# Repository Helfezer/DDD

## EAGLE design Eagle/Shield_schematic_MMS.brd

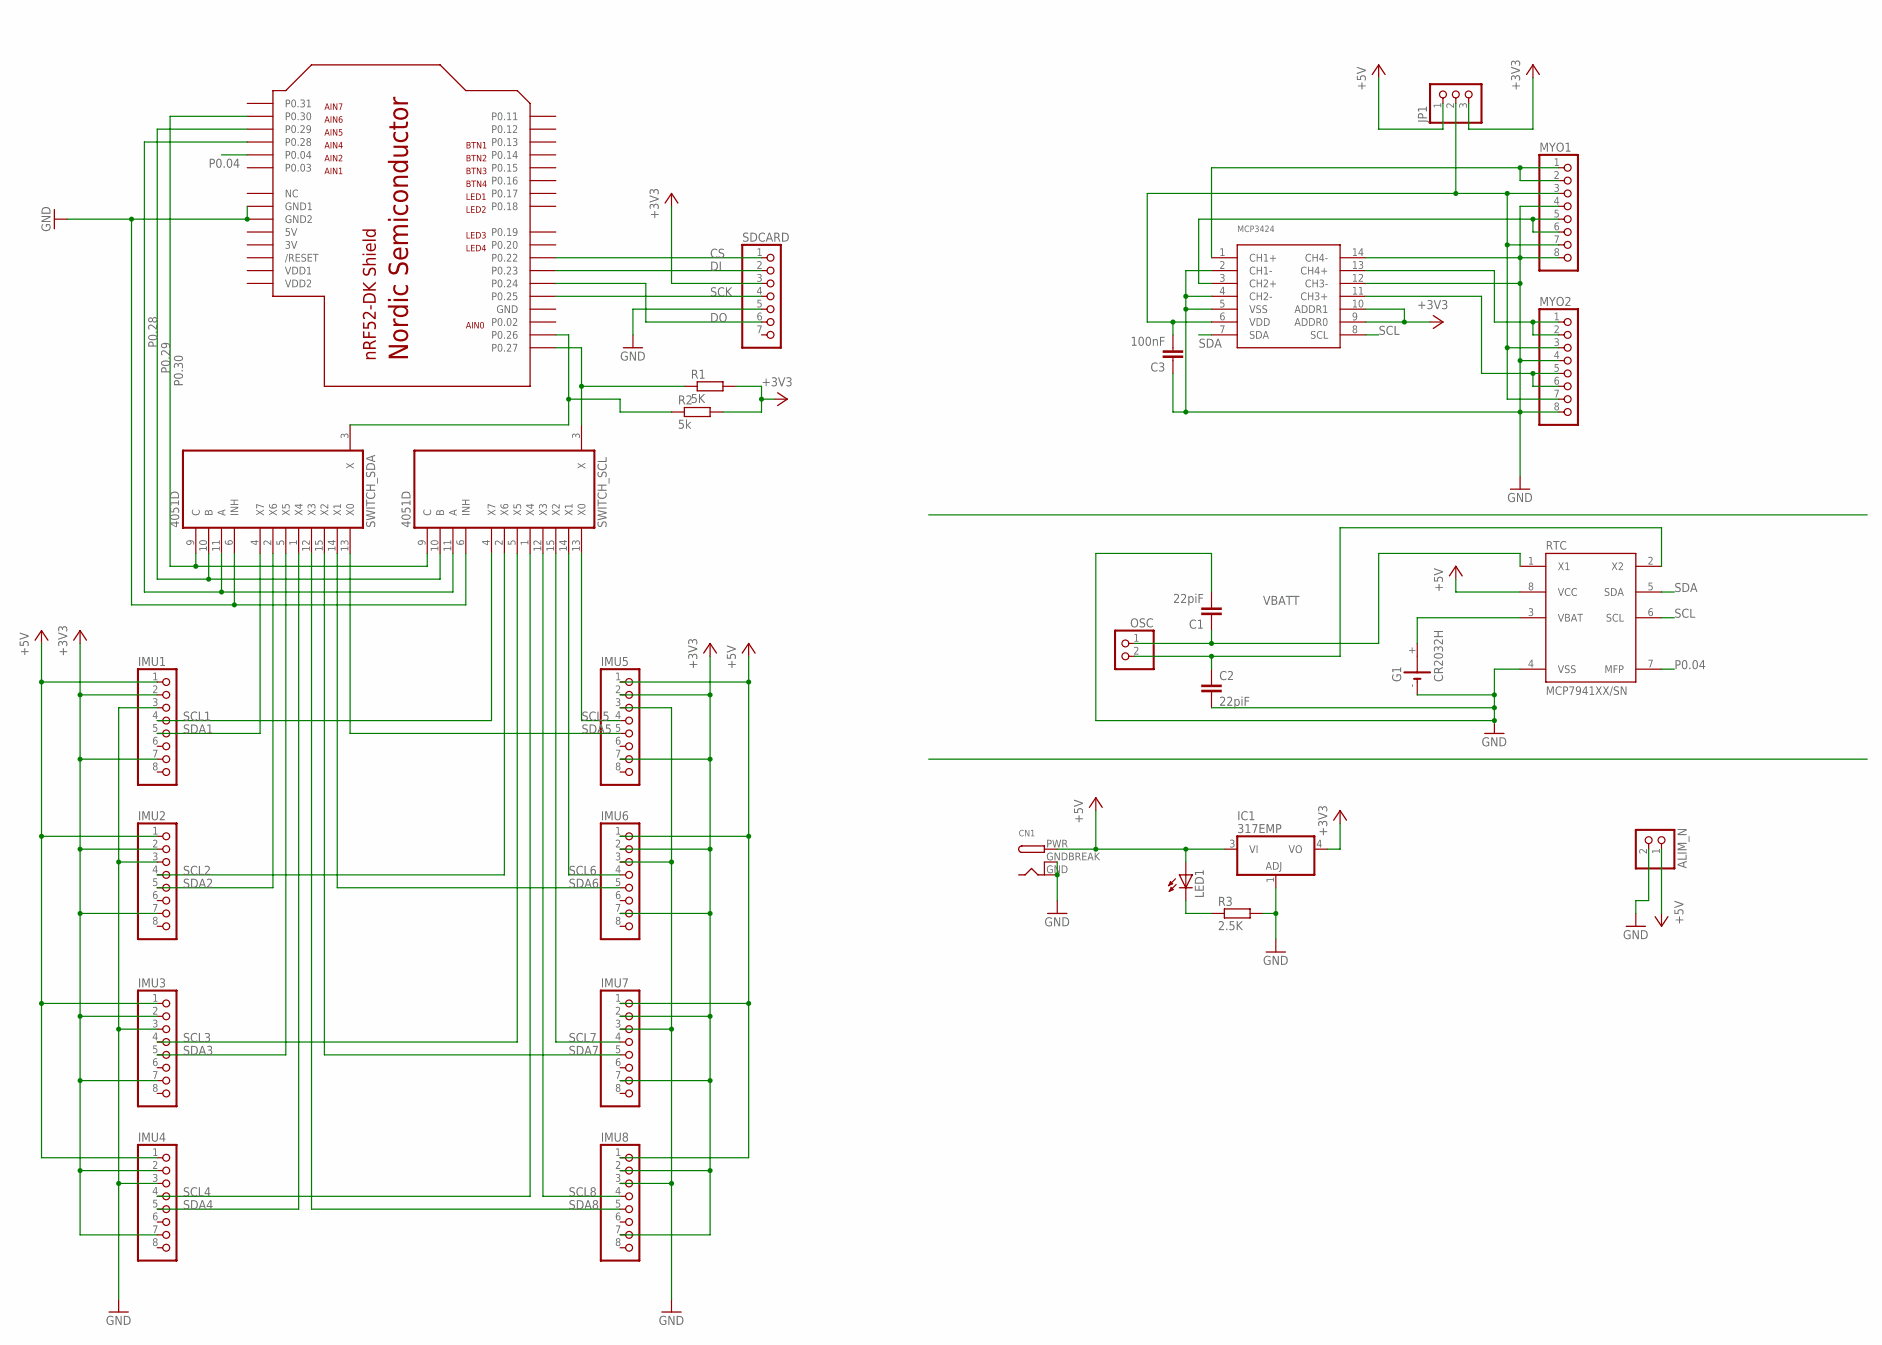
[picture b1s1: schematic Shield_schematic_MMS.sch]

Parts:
ALIM_N: PINHD-1X2; 1X02
C1, C2: 22piF; C2.5-2
C3: 100nF; C2.5-2
CN1: DCBARRELPTH; DCJACK_2MM_PTH
G1: CR2032H
IC1: 317EMP; SOT223
IMU1, IMU2, IMU3, IMU4, IMU5, IMU6, IMU7, IMU8: PINHD-1X8; 1X08
JP1: PINHD-1X3; 1X03
LED1: LEDCHIPLED_1206; CHIPLED_1206
MYO1, MYO2: PINHD-1X8; 1X08
OSC: PINHD-1X2; 1X02
R1: 5K; M1206
R2: 5k; M1206
R3: 2.5K; M1206
RTC: MCP7941XX/SN; SO8
SDCARD: PINHD-1X7; 1X07
SWITCH_SCL: 4051D; SO16
SWITCH_SDA: 4051D; SO16
U$2: NRF52-SHIELD-NOTEXT; NRF52-SHIELD
U$3: MCP3424; SO14

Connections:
3V: U$2.3V
5V: U$2.5V
+3V3: IC1.4 (VO), IMU1.2, IMU1.7, IMU2.2, IMU2.7, IMU3.2, IMU3.7, IMU4.2, IMU4.7, IMU5.2, IMU5.7, IMU6.2, IMU6.7, IMU7.2, IMU7.7, IMU8.2, IMU8.7, JP1.3, R1.2, R2.2, SDCARD.3, U$3.9 (ADDR0), U$3.10 (ADDR1)
+5V: ALIM_N.1, CN1.PWR, IC1.3 (VI), IMU1.1, IMU2.1, IMU3.1, IMU4.1, IMU5.1, IMU6.1, IMU7.1, IMU8.1, JP1.1, LED1.A, RTC.8 (VCC)
CH1: MYO1.1, MYO1.2, U$3.1 (CH1+)
CH2: MYO1.5, MYO1.6, U$3.3 (CH2+)
CH3: MYO2.5, MYO2.6, U$3.11 (CH3+)
CH4: MYO2.1, MYO2.2, U$3.13 (CH4+)
CS: SDCARD.1, U$2.P22 (P0.22)
DI: SDCARD.2, U$2.P23 (P0.23)
DO: SDCARD.6, U$2.P24 (P0.24)
GND: ALIM_N.2, C1.2, C2.2, C3.1, CN1.GND, CN1.GNDBREAK, G1.-, IC1.1 (ADJ), IMU1.3, IMU2.3, IMU3.3, IMU4.3, IMU5.3, IMU6.3, IMU7.3, IMU8.3, MYO1.4, MYO1.8, MYO2.4, MYO2.8, R3.2, RTC.4 (VSS), SDCARD.5, SWITCH_SCL.6 (INH), SWITCH_SCL.8 (GND), SWITCH_SDA.6 (INH), SWITCH_SDA.8 (GND), U$2.GND, U$2.GND1, U$2.GND2, U$3.2 (CH1-), U$3.4 (CH2-), U$3.5 (VSS), U$3.12 (CH3-), U$3.14 (CH4-)
unnamed: LED1.C, R3.1
P0.04: RTC.7 (MFP), U$2.P04 (P0.04)
P0.28: SWITCH_SCL.11 (A), SWITCH_SDA.11 (A), U$2.P28 (P0.28)
P0.29: SWITCH_SCL.10 (B), SWITCH_SDA.10 (B), U$2.P29 (P0.29)
P0.30: SWITCH_SCL.9 (C), SWITCH_SDA.9 (C), U$2.P30 (P0.30)
SCK: SDCARD.4, U$2.P25 (P0.25)
SCL: R1.1, RTC.6 (SCL), SWITCH_SCL.3 (X), U$2.P27 (P0.27), U$3.8 (SCL)
SCL1: IMU1.4, SWITCH_SCL.4 (X7)
SCL2: IMU2.4, SWITCH_SCL.2 (X6)
SCL3: IMU3.4, SWITCH_SCL.5 (X5)
SCL4: IMU4.4, SWITCH_SCL.1 (X4)
SCL5: IMU5.4, SWITCH_SCL.13 (X0)
SCL6: IMU6.4, SWITCH_SCL.14 (X1)
SCL7: IMU7.4, SWITCH_SCL.15 (X2)
SCL8: IMU8.4, SWITCH_SCL.12 (X3)
SDA: R2.1, RTC.5 (SDA), SWITCH_SDA.3 (X), U$2.P26 (P0.26), U$3.7 (SDA)
SDA1: IMU1.5, SWITCH_SDA.4 (X7)
SDA2: IMU2.5, SWITCH_SDA.2 (X6)
SDA3: IMU3.5, SWITCH_SDA.5 (X5)
SDA4: IMU4.5, SWITCH_SDA.1 (X4)
SDA5: IMU5.5, SWITCH_SDA.13 (X0)
SDA6: IMU6.5, SWITCH_SDA.14 (X1)
SDA7: IMU7.5, SWITCH_SDA.15 (X2)
SDA8: IMU8.5, SWITCH_SDA.12 (X3)
VBATT: G1.+, RTC.3 (VBAT)
VCC: SWITCH_SCL.16 (VCC), SWITCH_SDA.16 (VCC)
VDD: C3.2, JP1.2, MYO1.3, MYO1.7, MYO2.3, MYO2.7, U$3.6 (VDD)
VDD1: U$2.VDD2 (VDD1)
VDD2: U$2.VDD1 (VDD2)
VEE: SWITCH_SCL.7 (VEE), SWITCH_SDA.7 (VEE)
X1: C1.1, OSC.1, RTC.1 (X1)
X2: C2.1, OSC.2, RTC.2 (X2)

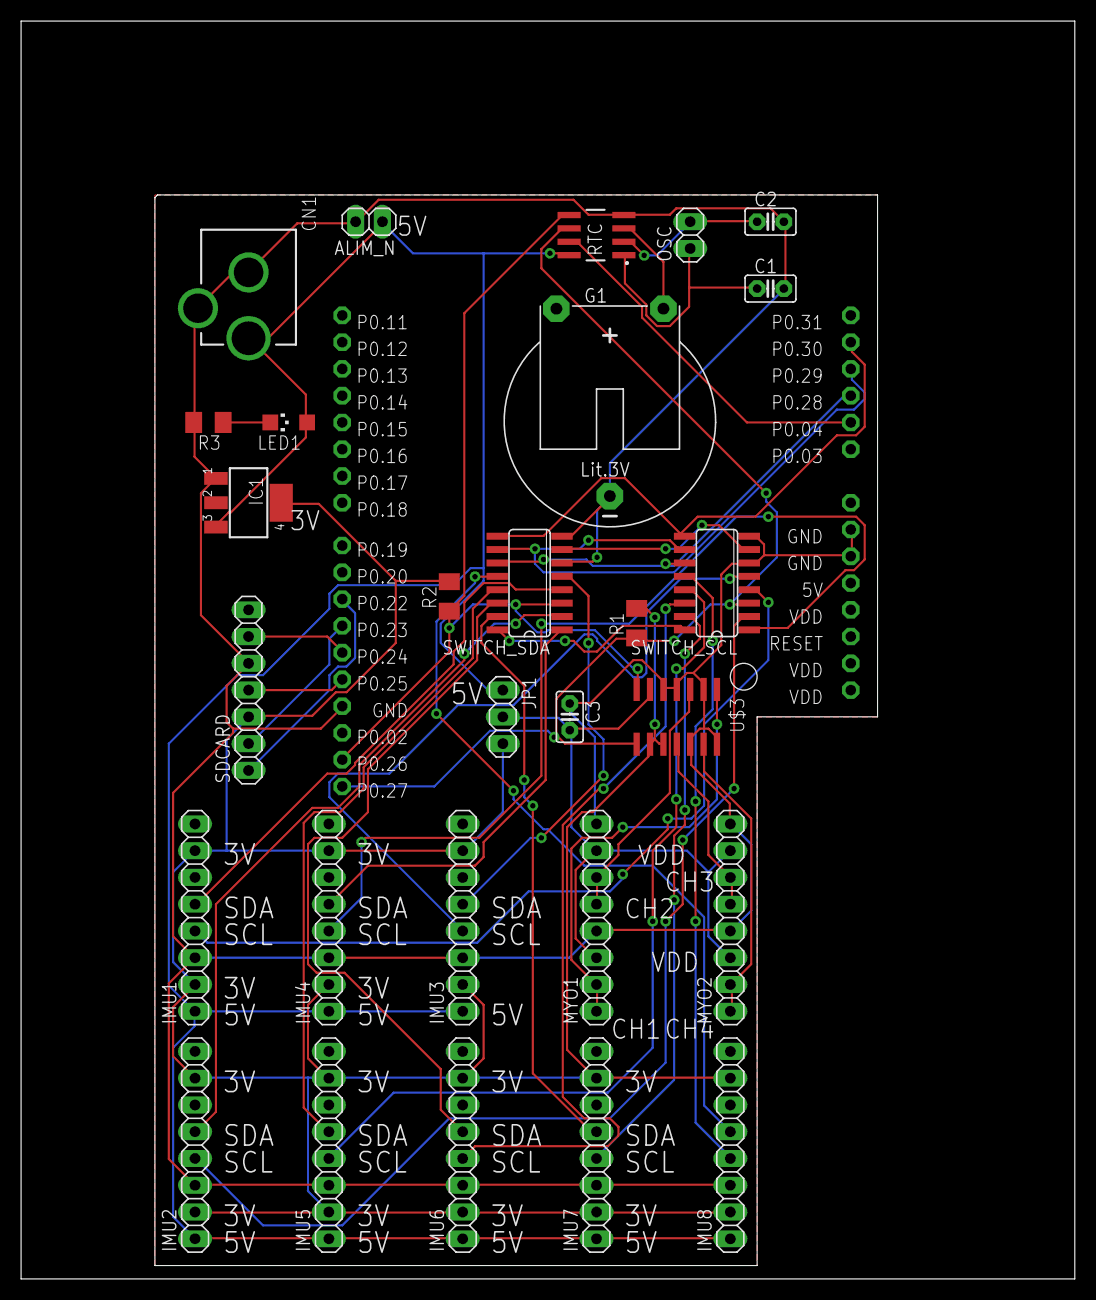
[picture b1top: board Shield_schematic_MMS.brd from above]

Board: 2 copper layers, 100.0 x 119.4 mm, 29 parts (0 on the bottom side), 40 nets.

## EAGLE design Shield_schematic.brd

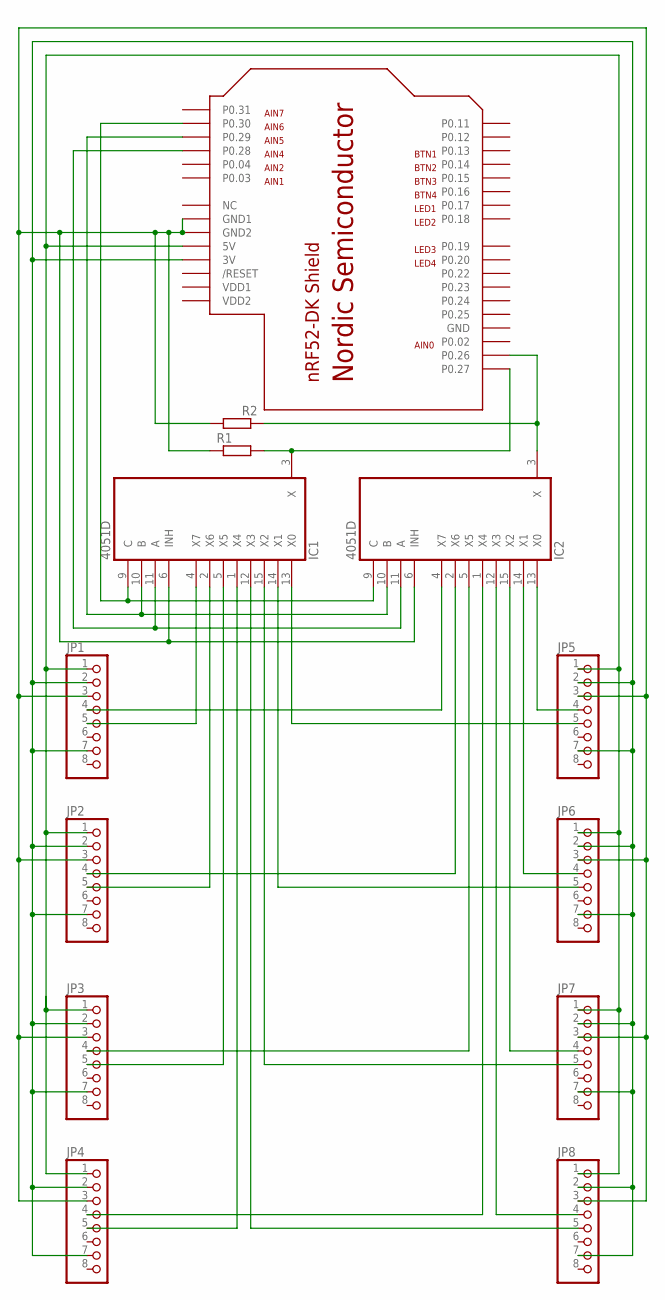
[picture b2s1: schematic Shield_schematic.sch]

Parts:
IC1, IC2: 4051D; SO16
JP1, JP2, JP3, JP4, JP5, JP6, JP7, JP8: PINHD-1X8; 1X08
R1, R2: R-EU_0411/15; 0411/15
U$1: NRF52-SHIELD-NOTEXT; NRF52-SHIELD

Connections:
GND: IC1.8 (GND), IC2.8 (GND), U$1.GND
unnamed: JP1.1, JP2.1, JP3.1, JP4.1, JP5.1, JP6.1, JP7.1, JP8.1, U$1.5V
unnamed: JP1.2, JP1.7, JP2.2, JP2.7, JP3.2, JP3.7, JP4.2, JP4.7, JP5.2, JP5.7, JP6.2, JP6.7, JP7.2, JP7.7, JP8.2, JP8.7, U$1.3V
unnamed: IC2.3 (X), R2.1, U$1.P26 (P0.26)
unnamed: IC2.13 (X0), JP5.4
unnamed: IC1.13 (X0), JP5.5
unnamed: IC1.14 (X1), JP6.5
unnamed: IC1.15 (X2), JP7.5
unnamed: IC1.12 (X3), JP8.5
unnamed: IC1.4 (X7), JP1.5
unnamed: IC1.2 (X6), JP2.5
unnamed: IC1.5 (X5), JP3.5
unnamed: IC1.1 (X4), JP4.5
unnamed: IC2.14 (X1), JP6.4
unnamed: IC2.15 (X2), JP7.4
unnamed: IC2.12 (X3), JP8.4
unnamed: IC2.1 (X4), JP4.4
unnamed: IC2.5 (X5), JP3.4
unnamed: IC2.2 (X6), JP2.4
unnamed: IC2.4 (X7), JP1.4
unnamed: IC1.11 (A), IC2.11 (A), U$1.P28 (P0.28)
unnamed: IC1.3 (X), R1.2, U$1.P27 (P0.27)
unnamed: IC1.10 (B), IC2.10 (B), U$1.P29 (P0.29)
unnamed: IC1.6 (INH), IC2.6 (INH), JP1.3, JP2.3, JP3.3, JP4.3, JP5.3, JP6.3, JP7.3, JP8.3, R1.1, R2.2, U$1.GND1, U$1.GND2
unnamed: IC1.9 (C), IC2.9 (C), U$1.P30 (P0.30)
VCC: IC1.16 (VCC), IC2.16 (VCC)
VDD1: U$1.VDD2 (VDD1)
VDD2: U$1.VDD1 (VDD2)
VEE: IC1.7 (VEE), IC2.7 (VEE)

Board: 2 copper layers, 13 parts (0 on the bottom side), 27 nets, no tracks yet.

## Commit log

2017-10-01 Creation du dépôt
2017-10-02 Datasheets
2017-10-07 These pour le projet 3D3
2017-10-09 Schéma Montage I2C + MPU6050
2017-10-09 Resume_reunion_1
2017-10-09 Cahier des charges
2017-10-12 Code Initial: exemple LM75B modifié, reception/envoi i2c
2017-10-12 maj Cahier_des_charges_V2
    + transformation rapport/ en document/
2017-10-13 erase shity file
2017-10-13 correct name for linux and add versionning doc
2017-10-17 add Resume et doc myoware
2017-11-06 Schema eagle
2017-11-06 Résumé de la semaine du 16/10/2017
2017-11-07 Save V0.1
2017-11-07 Save V0.2
2017-11-08 Doc freeRTOS + resum semaine
2017-11-08 Modif schematic (ajout 2éme switch)
2017-11-21 add datasheet ADC
2017-11-21 Add eagle directory + schema SD card
2017-12-07 Datasheet mcp3424 + lib eagle + doc plan rapport
2017-12-07 add mcp3424 sch in eagle
2017-12-09 Modif rapport
2018-01-14 ajout datasheet + annexe/ maj sch
2018-01-26 Piéce SW + board finaliser
2018-02-05 Derniére version Eagle
2018-02-07 Add: resumé semaine 13/10/2017 et descriptif des premiers tests
2018-02-07 MàJ premiere campagne de mesure
2018-02-20 ajout traitement python + donner mesurer
2018-03-16 Ajout 1ére salve de mesure + modif python
